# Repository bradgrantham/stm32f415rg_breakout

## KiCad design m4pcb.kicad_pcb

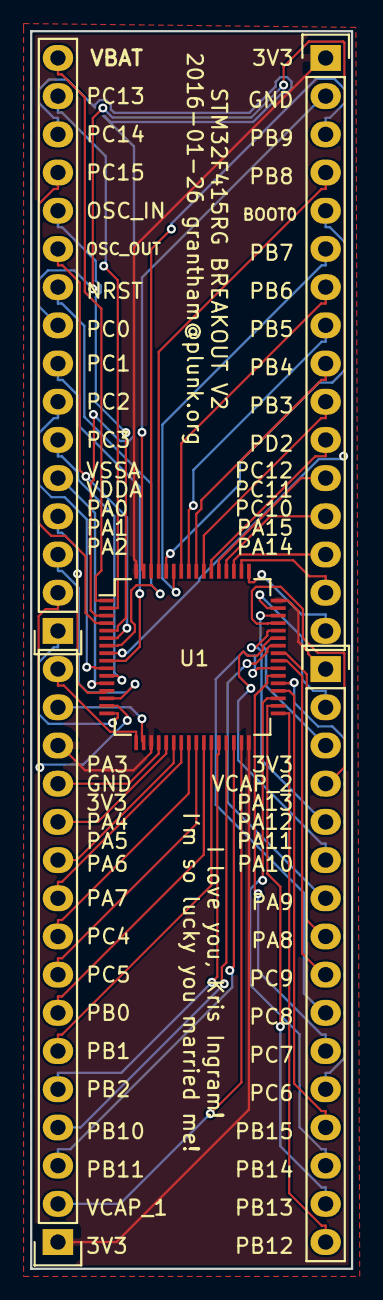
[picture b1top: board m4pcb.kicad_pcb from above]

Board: 2 copper layers, 21.3 x 82.3 mm, 5 parts (0 on the bottom side), 60 nets.

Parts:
P1, P2, P3, P4: CONN_01X16; Pin_Header_Straight_1x16
U1: STM32F415RG; LQFP-64_10x10mm_Pitch0.5mm

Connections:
3V3: P2.1, P2.14, P3.1, P4.1, U1.19, U1.32, U1.48, U1.64
BOOT0: P3.5, U1.60
GND: P2.15, P3.2, U1.18, U1.63
NRST: P1.10, U1.7
OSC_IN: P1.12, U1.5
OSC_OUT: P1.11, U1.6
PA0: P1.3, U1.14
PA1: P1.2, U1.15
PA2: P1.1, U1.16
PA3: P2.16, U1.17
PA4: P2.13, U1.20
PA5: P2.12, U1.21
PA6: P2.11, U1.22
PA7: P2.10, U1.23
PA8: P4.8, U1.41
PA9: P4.7, U1.42
PA10: P4.6, U1.43
PA11: P4.5, U1.44
PA12: P4.4, U1.45
PA13: P4.3, U1.46
PA14: P3.16, U1.49
PA15: P3.15, U1.50
PB0: P2.7, U1.26
PB1: P2.6, U1.27
PB2: P2.5, U1.28
PB3: P3.10, U1.55
PB4: P3.9, U1.56
PB5: P3.8, U1.57
PB6: P3.7, U1.58
PB7: P3.6, U1.59
PB8: P3.4, U1.61
PB9: P3.3, U1.62
PB10: P2.4, U1.29
PB11: P2.3, U1.30
PB12: P4.16, U1.33
PB13: P4.15, U1.34
PB14: P4.14, U1.35
PB15: P4.13, U1.36
PC0: P1.9, U1.8
PC1: P1.8, U1.9
PC2: P1.7, U1.10
PC3: P1.6, U1.11
PC4: P2.9, U1.24
PC5: P2.8, U1.25
PC6: P4.12, U1.37
PC7: P4.11, U1.38
PC8: P4.10, U1.39
PC9: P4.9, U1.40
PC10: P3.14, U1.51
PC11: P3.13, U1.52
PC12: P3.12, U1.53
PC13: P1.15, U1.2
PC14: P1.14, U1.3
PC15: P1.13, U1.4
PD2: P3.11, U1.54
VBAT: P1.16, U1.1
VCAP_1: P2.2, U1.31
VCAP_2: P4.2, U1.47
VDDA: P1.4, U1.13
VSSA: P1.5, U1.12

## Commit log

2016-01-27 m4pcb v1, sent to oshpark
2016-01-27 narrower, would've been 2 at oshpark
2016-02-18 fix labels, reroute GND/3V3
